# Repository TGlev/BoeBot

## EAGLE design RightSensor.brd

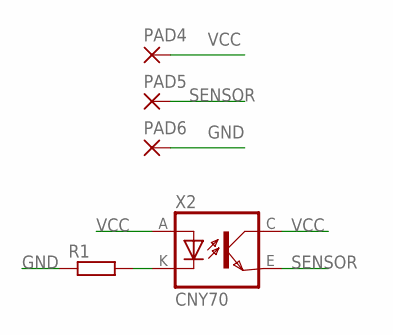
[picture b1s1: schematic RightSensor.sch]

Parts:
PAD4, PAD5, PAD6: WIREPADSMD1,27-254; SMD1,27-2,54
R1: RCL_R-EU_R0805; RCL_R0805
X2: CNY70; 4

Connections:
GND: PAD6.1, R1.1
unnamed: R1.2, X2.K (C)
SENSOR: PAD5.1, X2.E (EMI)
VCC: PAD4.1, X2.A, X2.C (COL)

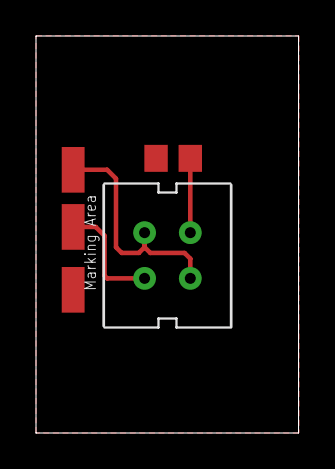
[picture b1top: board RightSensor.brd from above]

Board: 2 copper layers, 14.6 x 22.1 mm, 5 parts (0 on the bottom side), 4 nets.

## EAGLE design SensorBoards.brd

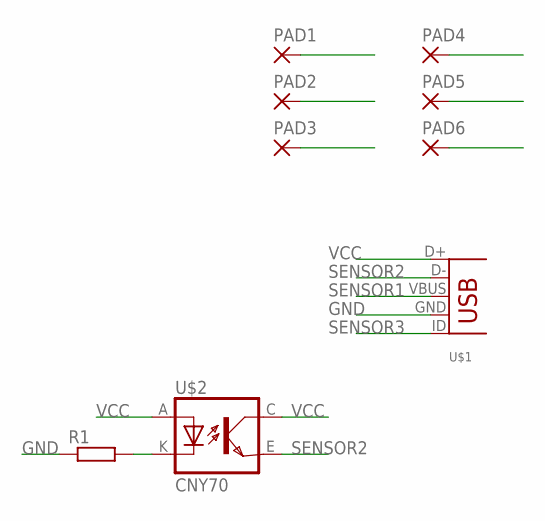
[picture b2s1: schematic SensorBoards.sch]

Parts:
PAD1, PAD2, PAD3, PAD4, PAD5, PAD6: WIREPADSMD2,54-5,08; SMD2,54-5,08
R1: RCL_R-EU_R0805; RCL_R0805
U$1: MOLES-USB-MICRO; MOLEX-USB-MICRO
U$2: CNY70; 4

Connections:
GND: PAD3.1, PAD6.1, R1.1, U$1.GND
unnamed: R1.2, U$2.K (C)
SENSOR1: PAD2.1, U$1.VBUS
SENSOR2: U$1.D-, U$2.E (EMI)
SENSOR3: PAD5.1, U$1.ID
VCC: PAD1.1, PAD4.1, U$1.D+, U$2.A, U$2.C (COL)

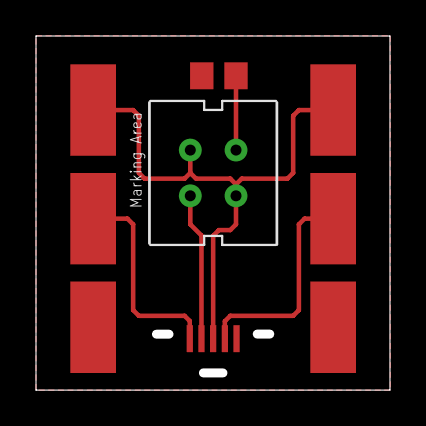
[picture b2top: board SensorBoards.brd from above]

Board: 2 copper layers, 19.7 x 19.7 mm, 9 parts (0 on the bottom side), 6 nets.

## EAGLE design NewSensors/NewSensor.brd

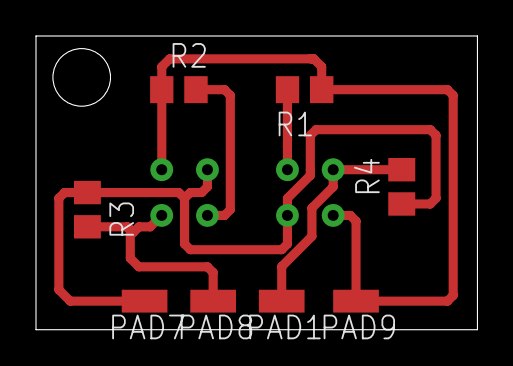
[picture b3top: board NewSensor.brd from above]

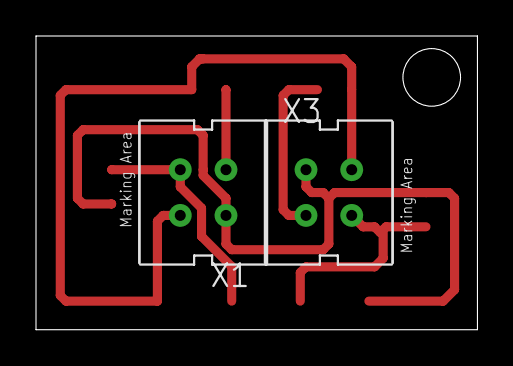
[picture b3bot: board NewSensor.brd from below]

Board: 2 copper layers, 24.5 x 16.3 mm, 10 parts (2 on the bottom side), 6 nets.

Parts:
PAD1, PAD7, PAD8, PAD9: WIREPADSMD1,27-254; SMD1,27-2,54
R1, R2, R3, R4: RCL_R0805
X1, X3: CNY70; 4

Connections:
GND_A: PAD9.1, R1.1, R2.1, X1.E, X3.E
unnamed: R1.2, X1.K
unnamed: R2.2, X3.K
SENSOR_A: PAD8.1, R3.2, X3.C
SENSOR_B: PAD1.1, R4.2, X1.C
VCC_A: PAD7.1, R3.1, R4.1, X1.A, X3.A

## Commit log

2018-10-07 First version.
    This version drives forward and stops when it notices an object. It will try to hit the object with its servo and then it continues to drive.
2018-10-09 First version of the PCBs
2018-10-10 Added sensor boards, started on proto frame design
2018-10-10 Updated boards
2018-10-31 Added code V1
2018-10-31 Added comments
2018-11-01 New sketch
